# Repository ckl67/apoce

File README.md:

/* =================================================================
	Pilote Arduino pour optimiser la gestion de consommation électrique
    Christian Klugesherz
    Date : 12 janvier 2025 --> Nouvelle approche avec double fonction de boutons
	
    Le schéma de la carte se trouve dans le répertoire Board
    La simulation se trouve sur
    https://www.tinkercad.com/things/i7El4JjrINq-pilote-contacteur
    L'Arduino Nano est basée sur l'ATmega328

    Code sous github : https://github.com/ckl67/apoce

	ATTENTION:
	===========
		Il est impératif de configurer la partie "Configuration" ci-dessous !
		
    Principe
    =========
    Entrée :
      * Signal Jour/Nuit - J/N
      * Signal Soleil - SOL
    Sortie :
      * Signal pour piloter contacteur Chauffe Eau 1 - CA1
      * Signal pour piloter contacteur Chauffe Eau 2 - CA2
      * Signal pour piloter contacteur Chargement Voiture - CV
	Bouton :
	  * BoutonJN --> Permet aussi de forcer CA1
	  * BoutonSOL--> Permet aussi de forcer CA2
	  * BoutonAUTO--> Permet aussi de forcer V
    Modes :
	  Dans le principe, un changement de mode, va re-initialiser le compteur d'armement

Les Modes disponibles :

	  -------------------------------------------
      * Mode JN : Jour-Nuit --> Led : Bleue Allumée
      --------------------------------------------
	 Si ModeArm = 0
        Si signal J/N = 1
            Basculement entre pilotage "CA1" puis "CA2" 
	 Si ModeArm = 1 
        Si signal J/N = 1
            Basculement entre pilotage "CA1" puis "CA2" puis "CV"  
		
    Si signal J/N = 0
          Pas de pilotage
		  
      -------------------------------------------
      * Mode SOL : Soleil --> Led Orange Allumée
      --------------------------------------------
    Si ModeArm = 0
        Si signal SOL = 1
          Basculement entre pilotage "CA1" puis "CA2"
	  Si ModeArm = 1 
        Si signal SOL = 1
          Basculement entre pilotage "CA1" puis "CA2" puis "CV"
    Si SOL = 0
          Pas de pilotage

      -------------------------------------------
      * Mode Auto : Jour-Nuit + Soleil --> Led Rouge Allumée
      --------------------------------------------
 	 Si ModeArm = 0
        Si signal SOL = 1 || Signal J/N = 1
          Basculement entre pilotage "CA1" puis "CA2"
	Si ModeArm = 1 
        Si signal SOL = 1 || Signal J/N = 1
          Basculement entre pilotage "CA1" puis "CA2" puis "CV"

	Si signal J/N = 0 ET SOL = 0
          Pas de pilotage
	
      -------------------------------------------
      * Bouton Armement pressé 1X --> Led Blanche Clignotante
      --------------------------------------------
		Quelque soit le mode : ModeArm = 1
			--> Nous intégrons la voiture dans le cycle 
			--> Nous utilisons la variable : SwitchContactSelection
			définie : ArmDuration
 
      -------------------------------------------
      * Bouton Armement pressé 2X --> Led Blanche Clignotante Rapide
      --------------------------------------------
			Quelque soit le mode : ModeArm = 2
				Sans courant de nuit, ni Soleil  : Basculement entre pilotage "CA1" puis "CA2" puis "V" sur une durée 
					définie : ArmDuration

      -------------------------------------------
      * Bouton Forcage JN=CA1 ou SOL=CA2 ou AUTO=V 
      -------------------------------------------
      Un premier appui sur le bouton va 
        * Positionner le forcage, 
      un deuxième va 
        * Positionner le mode

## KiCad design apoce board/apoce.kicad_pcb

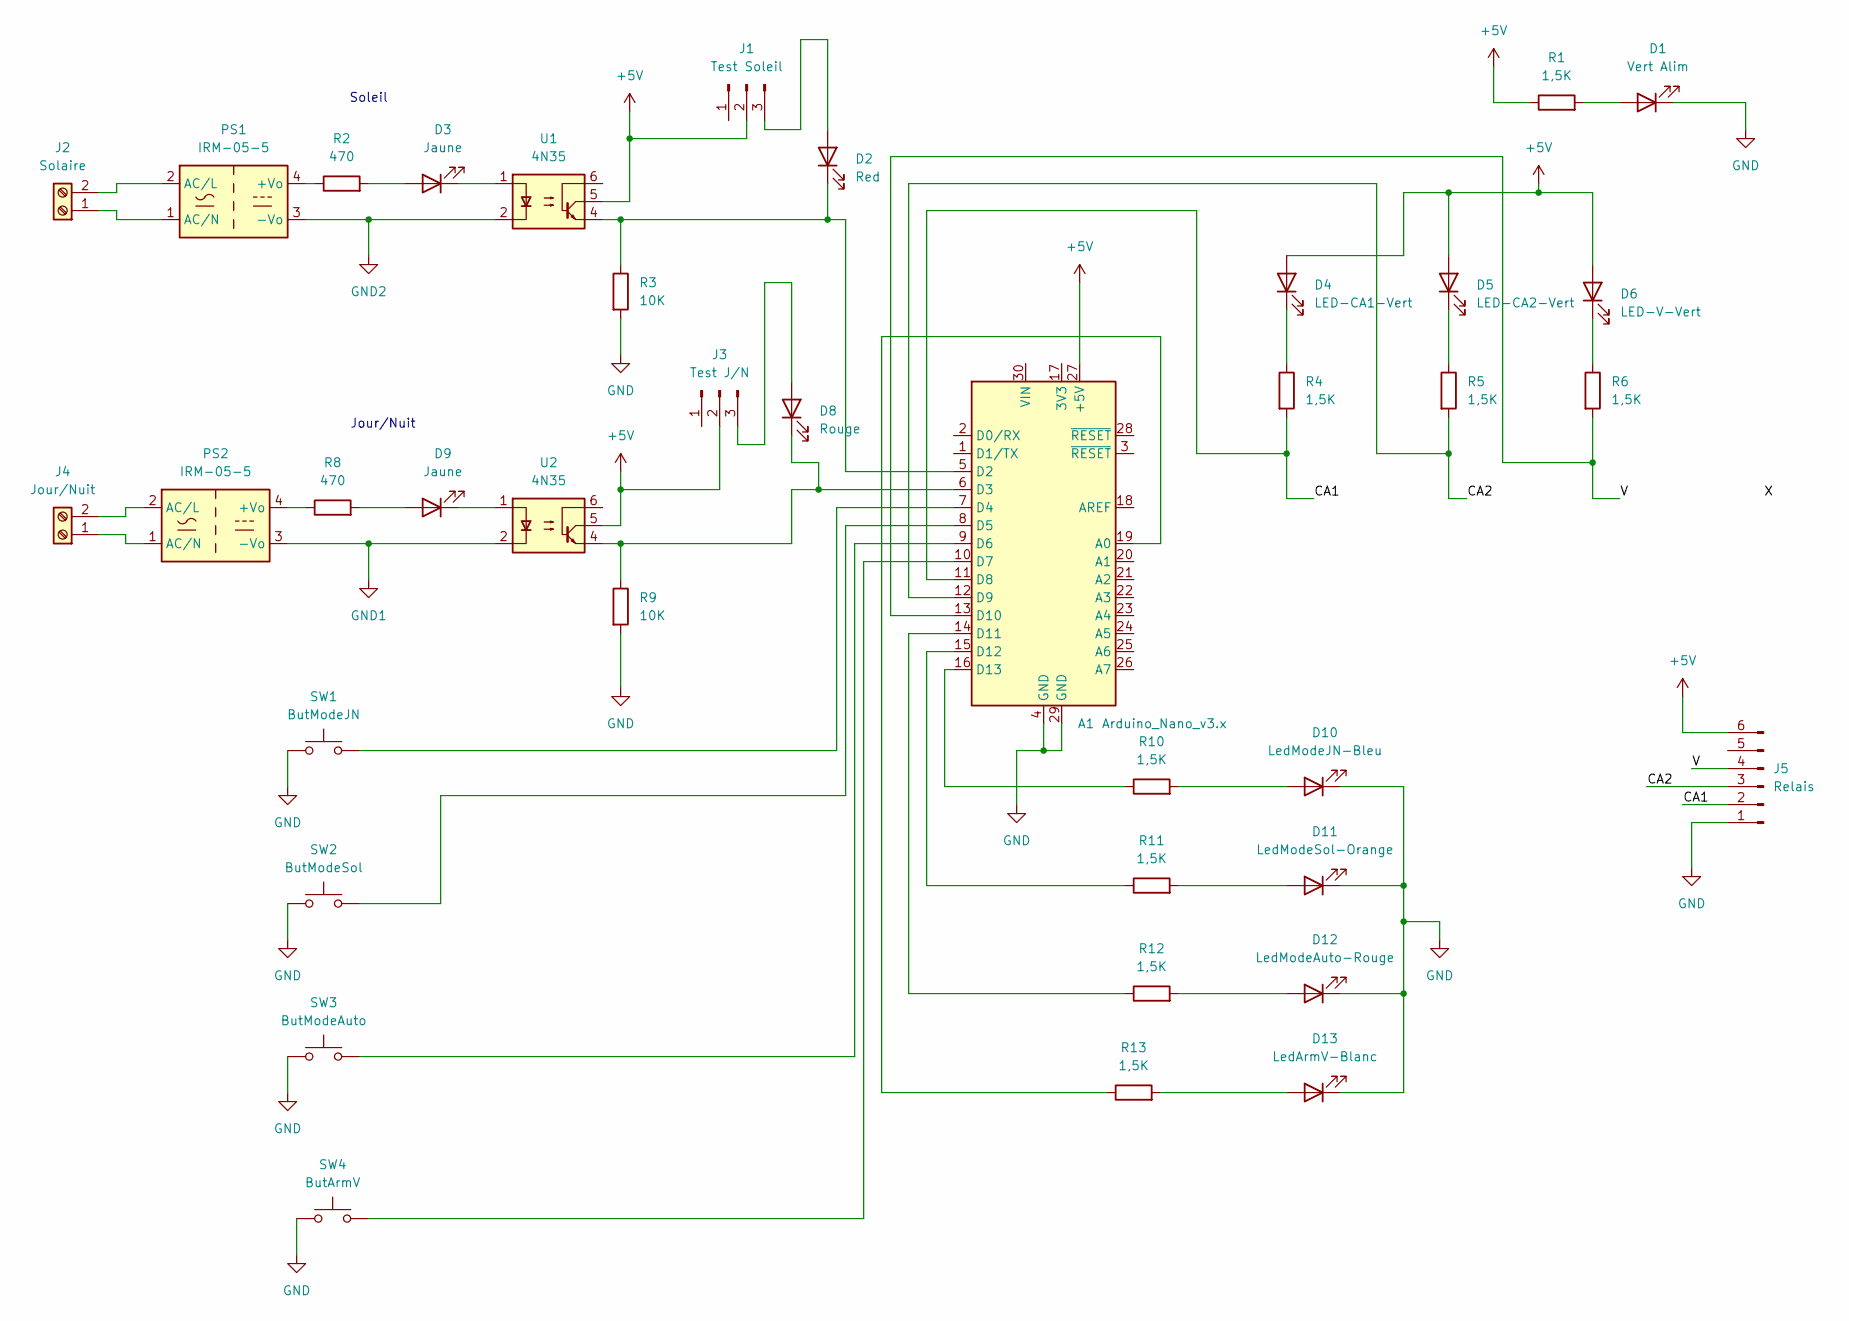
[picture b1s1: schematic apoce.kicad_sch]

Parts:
A1: Arduino_Nano_v3.x; Arduino_Nano
D1: Vert Alim; LED_D5.0mm
D2: Red; LED_D5.0mm
D3, D9: Jaune; LED_D5.0mm
D4: LED-CA1-Vert; LED_D5.0mm
D5: LED-CA2-Vert; LED_D5.0mm
D6: LED-V-Vert; LED_D5.0mm
D8: Rouge; LED_D5.0mm
D10: LedModeJN-Bleu; LED_D5.0mm
D11: LedModeSol-Orange; LED_D5.0mm
D12: LedModeAuto-Rouge; LED_D5.0mm
D13: LedArmV-Blanc; LED_D5.0mm
J1: Test Soleil; TerminalBlock_Xinya_XY308-2.54-3P_1x03_P2.54mm_Horizontal
J2: Solaire; TerminalBlock_Phoenix_MKDS-1,5-2-5.08_1x02_P5.08mm_Horizont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
J3: Test J/N; TerminalBlock_Xinya_XY308-2.54-3P_1x03_P2.54mm_Horizontal
J4: Jour/Nuit; TerminalBlock_bornier-2_P5.08mm
J5: Relais; TerminalBlock_Xinya_XY308-2.54-6P_1x06_P2.54mm_Horizontal
PS1, PS2: IRM-05-5; Converter_ACDC_MeanWell_IRM-05-xx_THT
R1, R4, R5, R6, R10, R11, R12, R13: 1,5K; R_Axial_DIN0207_L6.3mm_D2.5mm_P10.16mm_Horizontal
R2, R8: 470; R_Axial_DIN0207_L6.3mm_D2.5mm_P10.16mm_Horizontal
R3, R9: 10K; R_Axial_DIN0207_L6.3mm_D2.5mm_P10.16mm_Horizontal
SW1: ButModeJN; TerminalBlock_Phoenix_MKDS-1,5-2-5.08_1x02_P5.08mm_Horizont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
SW2: ButModeSol; TerminalBlock_Phoenix_MKDS-1,5-2-5.08_1x02_P5.08mm_Horizont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
SW3: ButModeAuto; TerminalBlock_Phoenix_MKDS-1,5-2-5.08_1x02_P5.08mm_Horizont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
SW4: ButArmV; TerminalBlock_Phoenix_MKDS-1,5-2-5.08_1x02_P5.08mm_Horizont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
U1, U2: 4N35; DIP-6_W7.62mm_LongPads

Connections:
+5V: A1.27 (+5V), D4.2 (A), D5.2 (A), D6.2 (A), J1.2, J3.2, J5.6, R1.1, U1.5, U2.5
/CA1: A1.11 (D8), J5.2, R4.2
/CA2: A1.12 (D9), J5.3, R5.2
/V: A1.13 (D10), J5.4, R6.2
GND: A1.4 (GND), A1.29 (GND), D1.1 (K), D10.1 (K), D11.1 (K), D12.1 (K), D13.1 (K), J5.1, R3.2, R9.2, SW1.1, SW2.1, SW3.1, SW4.1
GND1: PS2.3 (-Vo), U2.2
GND2: PS1.3 (-Vo), U1.2
unnamed: A1.19 (A0), R13.1
unnamed: A1.5 (D2), D2.1 (K), R3.1, U1.4
unnamed: A1.6 (D3), D8.1 (K), R9.1, U2.4
unnamed: A1.7 (D4), SW1.2
unnamed: A1.8 (D5), SW2.2
unnamed: A1.9 (D6), SW3.2
unnamed: A1.10 (D7), SW4.2
unnamed: A1.14 (D11), R12.1
unnamed: A1.15 (D12), R11.1
unnamed: A1.16 (D13), R10.1
unnamed: D1.2 (A), R1.2
unnamed: D2.2 (A), J1.3
unnamed: D3.2 (A), R2.2
unnamed: D3.1 (K), U1.1
unnamed: D4.1 (K), R4.1
unnamed: D5.1 (K), R5.1
unnamed: D6.1 (K), R6.1
unnamed: D8.2 (A), J3.3
unnamed: D9.2 (A), R8.2
unnamed: D9.1 (K), U2.1
unnamed: D10.2 (A), R10.2
unnamed: D11.2 (A), R11.2
unnamed: D12.2 (A), R12.2
unnamed: D13.2 (A), R13.2
unnamed: J2.1, PS1.1 (AC/N)
unnamed: J2.2, PS1.2 (AC/L)
unnamed: J4.1, PS2.1 (AC/N)
unnamed: J4.2, PS2.2 (AC/L)
unnamed: PS1.4 (+Vo), R2.1
unnamed: PS2.4 (+Vo), R8.1

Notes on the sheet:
Jour/Nuit
Soleil

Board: 2 copper layers, 38 parts (0 on the bottom side), 37 nets, no tracks yet.

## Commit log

2024-05-27 Premier commit
2024-05-27 test
2024-05-27 Version fonctionnelle qui prend en compte le deuxième armement
2024-05-31 Explication Pull-UP
2024-06-02 Test avec Sourcetree
2024-06-03 Ajout méthode de permutation de la valeur de tempo à travers l'appui des 3 boutons
2024-06-03 Petite correction pour permettre la gestion des 3 boutons
2024-06-03 Correction Bug 3 boutons
2024-08-15 no message
2024-08-15 Augmente temps interval à 30 minutes
2024-08-15 Ajout Carte
2024-08-15 Etape 1 pour le placement routage
2024-10-10 Nouvelle mouture complétement refaite avec une plus grande faclité pour gérer le bouton Armement
2025-01-05 Nouvelle version avec amélioration
2025-01-08 Revert "Nouvelle version avec amélioration"
    This reverts commit 7894d477df82a93182f71be82a563ec3e50d3505.
2025-01-08 Reapply "Nouvelle version avec amélioration"
    This reverts commit de40c29c87853ffb3fdf9fb958bdbe0331c75c98.
2025-01-08 Nouvelle approche en mode multiple
2025-01-12 testt
2025-01-12 Préparation à travers une logique de controle
    #define BitForceCA1 0x3 // Force Mode CA1
    #define BitForceCA2 0x2 // Force Mode CA2
    #define BitForceV 0x1 // Force Mode Voiture
2025-01-12 On a séparer les compteurs Led de forcage
2025-01-12 Version fonctionelle
2025-01-13 Nouvelle version Stable
2025-01-13 Modification doc
